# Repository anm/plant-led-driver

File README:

This was designed for grow light but obviously can be rather more general
purpose.

I have made one and it works.

Software incomplete, but may clean up / publish at some point, especially if
there is interest. I didn't do modbus yet but the 485 link works with custom
commands. It could also be persuaded to understand DMX, I believe.

Some idiosyncracities in design becasue of what parts I had. The 5V supply is
just for the MAX485. You could use a MAX3485 or other 3.3V part.

The electrolytic caps and inrush NTC are not needed.

I only tested it up to 700mA (nominal) per channel.

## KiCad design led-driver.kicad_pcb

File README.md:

This was designed for grow light but obviously can be rather more general
purpose. I have made one and it works.

Drivers are PAM2863, controller STM32G030F6P6.

Software incomplete, but may clean up / publish at some point, especially if
there is interest. I didn't do modbus yet but the 485 link works with custom
commands. It could also be persuaded to understand DMX, I believe.

Some idiosyncracities in design becasue of what parts I had. The 5V supply is
just for the MAX485. You could use a MAX3485 or other 3.3V part. The board is
<100x100mm for cheap manufacture, and the components are cheap from LCSC. The
throughhole stuff could be made SMD for cheap manufacture, but I made this for
assembling myself with parts I had.

The electrolytic caps and inrush NTC are not needed.

I designed it for, and tested it up to, 700mA (nominal) per channel. The
drivers can do 2A, and the specified components should also work at 2A, except
that you need to change the current sense resistor to change the maximum
current. Choose resistance according to the table in the datasheet or on the
back of the board, with sufficient power dissapation.

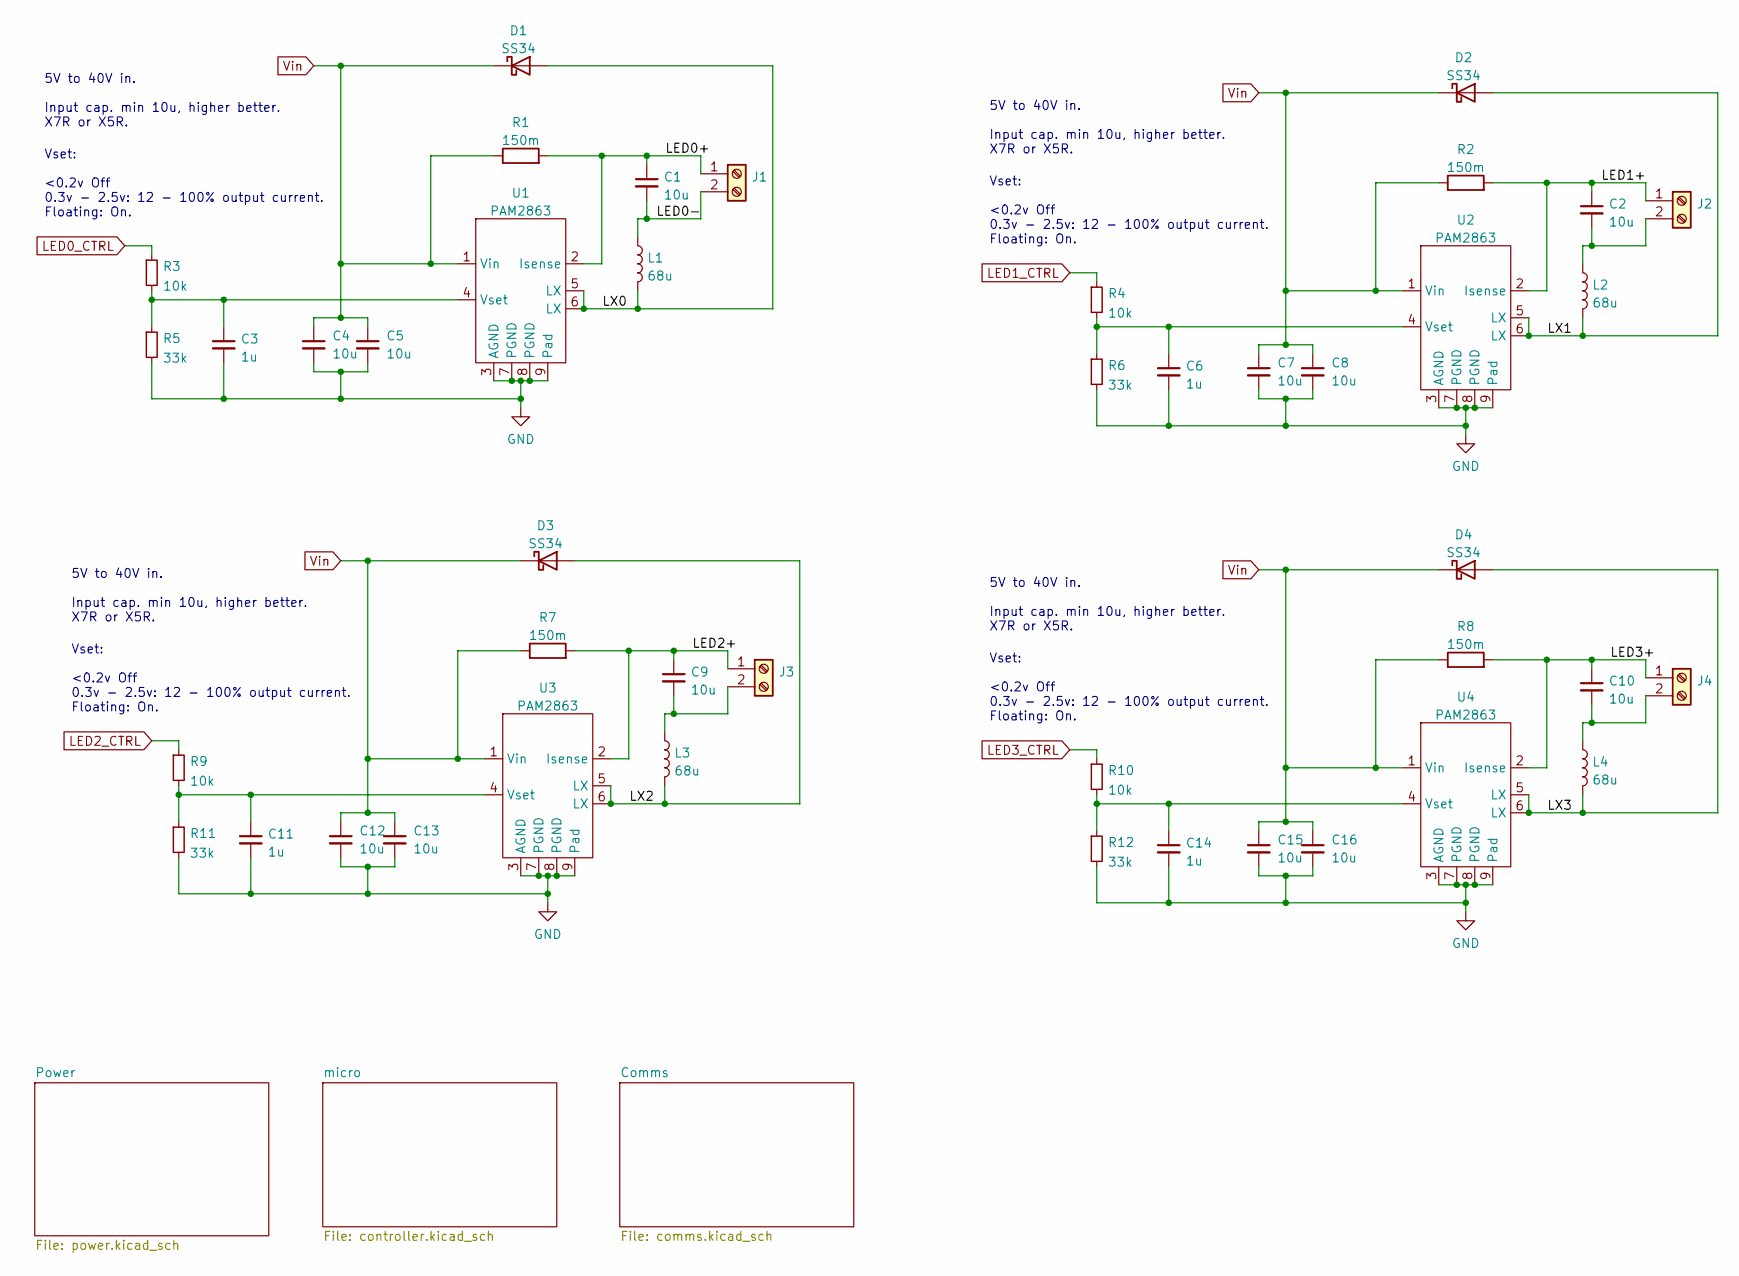
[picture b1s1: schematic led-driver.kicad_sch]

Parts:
C1, C2, C4, C5, C7, C8, C9, C10, C12, C13, C15, C16: 10u; C_1206_3216Metric_Pad1.33x1.80mm_HandSolder; LCSC# C89632
C3, C6, C11, C14: 1u; C_0805_2012Metric
D1, D2, D3, D4: SS34; D_SMA; Part# Slkor SS34; LCSC# C408258
J1, J2, J3, J4: TerminalBlock_KEFENG_Blue_2
L1, L2, L3, L4: 68u; Inductor_SMD_10.2x11.0x5; LCSC# C2837473
R1, R2, R7, R8: 150m; R_2010_5025Metric_Pad1.40x2.65mm_HandSolder; LCSC# C382266
R3, R4, R9, R10: 10k; R_0805_2012Metric
R5, R6, R11, R12: 33k; R_0805_2012Metric
U1, U2, U3, U4: PAM2863; HSOP-8-1EP_3.9x4.9mm_P1.27mm_EP2.41x3.1mm_ThermalVias_0.3mm

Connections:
/LED0+: C1.1, J1.1, R1.2, U1.2 (Isense)
/LED0-: C1.2, J1.2, L1.1
/LED1+: C2.1, J2.1, R2.2, U2.2 (Isense)
/LED2+: C9.1, J3.1, R7.2, U3.2 (Isense)
/LED3+: C10.1, J4.1, R8.2, U4.2 (Isense)
/LX0: D1.2 (A), L1.2, U1.5 (LX), U1.6 (LX)
/LX1: D2.2 (A), L2.2, U2.5 (LX), U2.6 (LX)
/LX2: D3.2 (A), L3.2, U3.5 (LX), U3.6 (LX)
/LX3: D4.2 (A), L4.2, U4.5 (LX), U4.6 (LX)
GND: C3.2, C4.2, C5.2, C6.2, C7.2, C8.2, C11.2, C12.2, C13.2, C14.2, C15.2, C16.2, R5.2, R6.2, R11.2, R12.2, U1.3 (AGND), U1.7 (PGND), U1.8 (PGND), U1.9 (Pad), U2.3 (AGND), U2.7 (PGND), U2.8 (PGND), U2.9 (Pad), U3.3 (AGND), U3.7 (PGND), U3.8 (PGND), U3.9 (Pad), U4.3 (AGND), U4.7 (PGND), U4.8 (PGND), U4.9 (Pad); also elsewhere on the board
LED0_CTRL: R3.1; also elsewhere on the board
LED1_CTRL: R4.1; also elsewhere on the board
LED2_CTRL: R9.1; also elsewhere on the board
LED3_CTRL: R10.1; also elsewhere on the board
unnamed: C2.2, J2.2, L2.1
unnamed: C3.1, R3.2, R5.1, U1.4 (Vset)
unnamed: C6.1, R4.2, R6.1, U2.4 (Vset)
unnamed: C9.2, J3.2, L3.1
unnamed: C10.2, J4.2, L4.1
unnamed: C11.1, R9.2, R11.1, U3.4 (Vset)
unnamed: C14.1, R10.2, R12.1, U4.4 (Vset)
Vin: C4.1, C5.1, C7.1, C8.1, C12.1, C13.1, C15.1, C16.1, D1.1 (K), D2.1 (K), D3.1 (K), D4.1 (K), R1.1, R2.1, R7.1, R8.1, U1.1 (Vin), U2.1 (Vin), U3.1 (Vin), U4.1 (Vin); also elsewhere on the board

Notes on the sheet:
Vset: <0.2v Off 0.3v - 2.5v: 12 - 100% output current. Floating: On.
5V to 40V in. Input cap. min 10u, higher better. X7R or X5R.

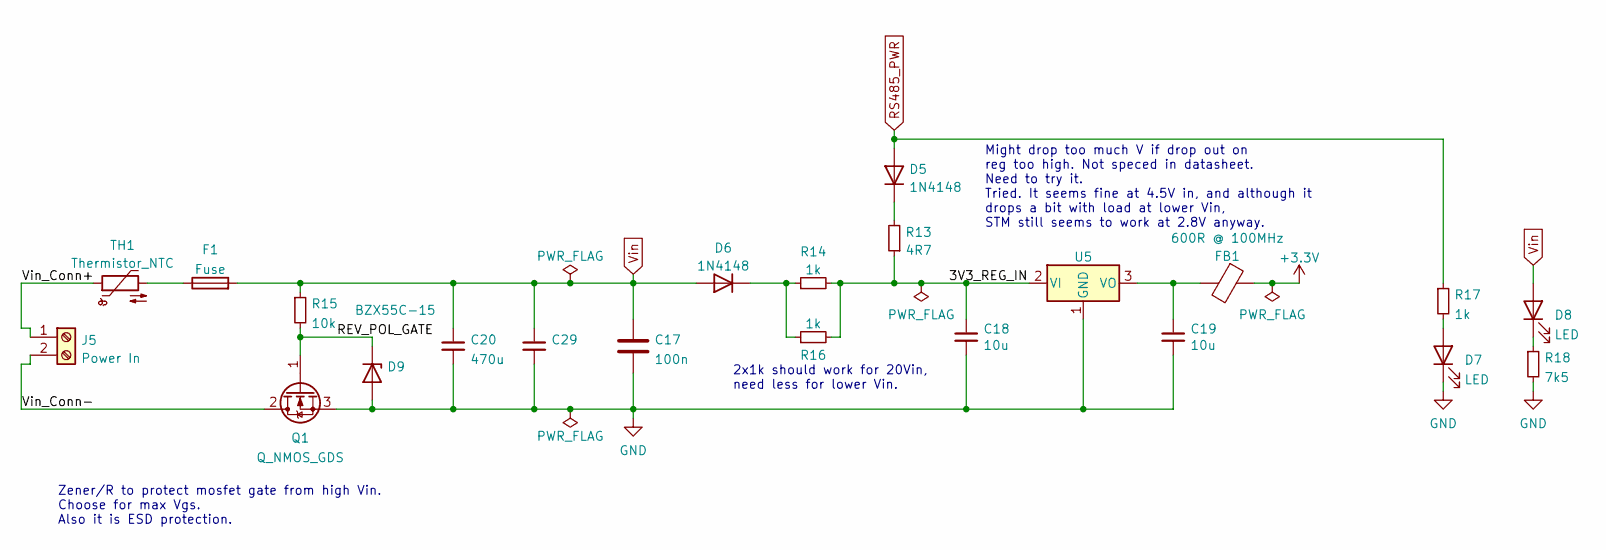
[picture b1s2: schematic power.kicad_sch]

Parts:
C17: 100n; C_0805_2012Metric
C18, C19: 10u; C_0805_2012Metric; Part# CL21A106KAYNNNE; LCSC# C15850
C20: 470u; CP_Radial_D10.0mm_P5.00mm
C29: CP_Radial_D10.0mm_P5.00mm
D5, D6: 1N4148; D_DO-35_SOD27_P7.62mm_Horizontal
D7, D8: LED; LED_0805_2012Metric
D9: BZX55C-15; D_DO-35_SOD27_P7.62mm_Horizontal
F1: Fuse; Fuseholder_Cylinder-5x20mm_Schurter_0031_8201_Horizontal_Op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
FB1: 600R @ 100MHz; L_0805_2012Metric; Part# GZ2012D601TF; LCSC# C1017
J5: Power In; TerminalBlock_KEFENG_Blue_2
Q1: Q_NMOS_GDS; TO-252-3_TabPin2; Part Overspecced but I have some NVD5865NL
R13: 4R7; R_Axial_DIN0309_L9.0mm_D3.2mm_P12.70mm_Horizontal
R14, R16: 1k; R_Axial_DIN0309_L9.0mm_D3.2mm_P12.70mm_Horizontal
R15: 10k; R_0805_2012Metric_Pad1.20x1.40mm_HandSolder
R17: 1k; R_0805_2012Metric
R18: 7k5; R_0805_2012Metric
TH1: Thermistor_NTC; C_Disc_D7.5mm_W5.0mm_P7.50mm
U5: UMW_HT7533-1_3.3V_High-In_LDO_SOT89; SOT-89-3

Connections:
+3V3: FB1.1; also elsewhere on the board
/Power/3V3_REG_IN: C18.1, R13.1, R14.2, R16.2, U5.2 (VI)
/Power/REV_POL_GATE: D9.1 (K), Q1.1 (G), R15.2
/Power/Vin_Conn+: J5.1, TH1.1
/Power/Vin_Conn-: J5.2, Q1.2 (D)
GND: C17.2, C18.2, C19.2, C20.2, C29.2, D7.1 (K), D9.2 (A), Q1.3 (S), R18.2, U5.1 (GND); also elsewhere on the board
unnamed: C19.1, FB1.2, U5.3 (VO)
unnamed: D5.1 (K), R13.2
unnamed: D6.1 (K), R14.1, R16.1
unnamed: D7.2 (A), R17.2
unnamed: D8.1 (K), R18.1
unnamed: F1.1, TH1.2
RS485_PWR: D5.2 (A), R17.1; also elsewhere on the board
Vin: C17.1, C20.1, C29.1, D6.2 (A), D8.2 (A), F1.2, R15.1; also elsewhere on the board

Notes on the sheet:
Might drop too much V if drop out on reg too high. Not speced in datasheet. Need to try it. Tried. It seems fine at 4.5V in, and although it drops a bit with load at lower Vin, STM still seems to work at 2.8V anyway.
2x1k should work for 20Vin, need less for lower Vin.
Zener/R to protect mosfet gate from high Vin. Choose for max Vgs. Also it is ESD protection.

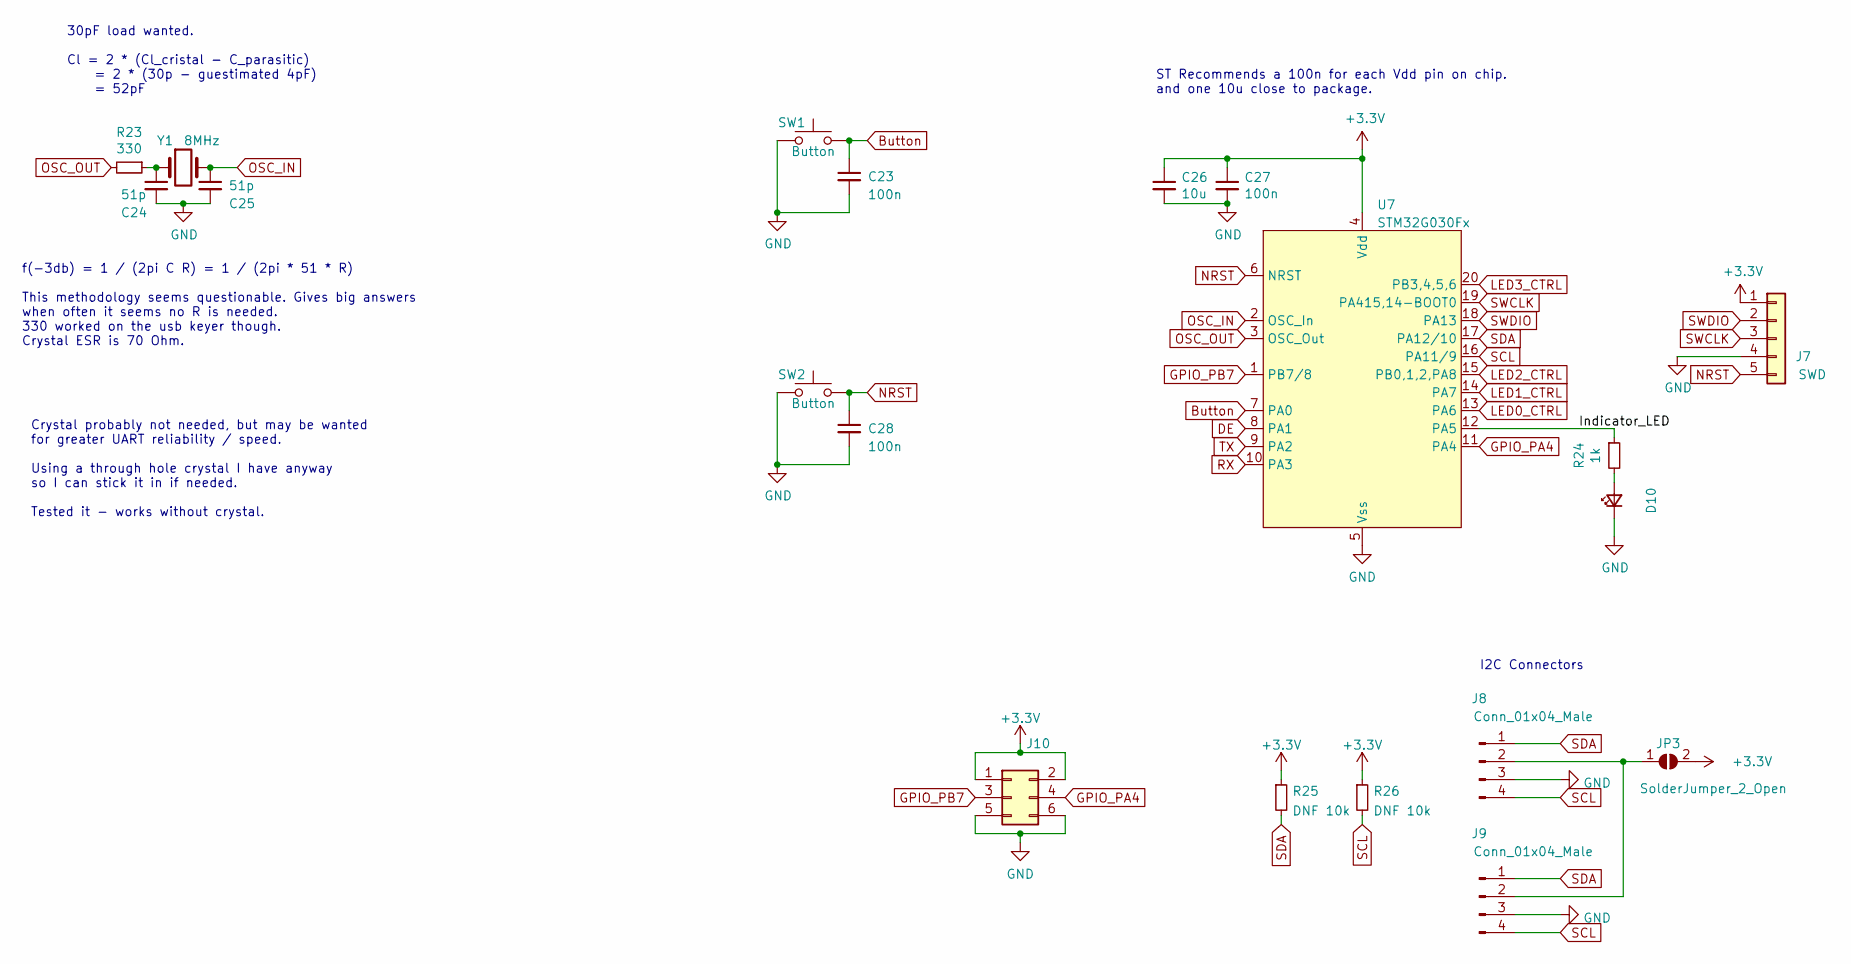
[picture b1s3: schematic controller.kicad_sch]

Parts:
C23, C27, C28: 100n; C_0805_2012Metric; Part# CL05B104KO5NNNC; LCSC# C1525
C24, C25: 51p; C_0603_1608Metric_Pad1.08x0.95mm_HandSolder
C26: 10u; C_0805_2012Metric; Part# CL21A106KAYNNNE; LCSC# C15850
D10: LED_0805_2012Metric; LCSC# C2297
J7: SWD; PinHeader_1x05_P2.54mm_Vertical
J8, J9: Conn_01x04_Male; JST_PH_B4B-PH-K_1x04_P2.00mm_Vertical
J10: Conn_02x03_Counter_Clockwise; PinHeader_2x03_P2.54mm_Vertical
JP3: SolderJumper_2_Open; SolderJumper-2_P1.3mm_Open_TrianglePad1.0x1.5mm
R23: 330; R_0805_2012Metric; LCSC# C17630
R24: 1k; R_0805_2012Metric; LCSC# C17590
R25, R26: DNF 10k; R_0805_2012Metric_Pad1.20x1.40mm_HandSolder
SW1, SW2: Button; SW_SPST_TL3342; LCSC# C412369
U7: STM32G030Fx; TSSOP-20_4.4x6.5mm_P0.65mm
Y1: 8MHz; Crystal_HC49-4H_Vertical

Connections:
+3V3: C26.1, C27.1, J7.1, J10.1, J10.2, JP3.2 (B), R25.1, R26.1, U7.4 (Vdd); also elsewhere on the board
/micro/Indicator_LED: R24.1, U7.12 (PA5)
Button: C23.1, SW1.2, U7.7 (PA0)
DE: U7.8 (PA1); also elsewhere on the board
GND: C23.2, C24.2, C25.2, C26.2, C27.2, C28.2, D10.1 (K), J7.4, J8.3, J9.3, J10.5, J10.6, SW1.1, SW2.1, U7.5 (Vss); also elsewhere on the board
GPIO_PA4: J10.4, U7.11 (PA4)
GPIO_PB7: J10.3, U7.1 (PB7/8)
LED0_CTRL: U7.13 (PA6); also elsewhere on the board
LED1_CTRL: U7.14 (PA7); also elsewhere on the board
LED2_CTRL: U7.15 (PB0,1,2,PA8); also elsewhere on the board
LED3_CTRL: U7.20 (PB3,4,5,6); also elsewhere on the board
NRST: C28.1, J7.5, SW2.2, U7.6 (NRST)
unnamed: C24.1, R23.1, Y1.1
unnamed: D10.2 (A), R24.2
unnamed: J8.2, J9.2, JP3.1 (A)
OSC_IN: C25.1, U7.2 (OSC_In), Y1.2
OSC_OUT: R23.2, U7.3 (OSC_Out)
RX: U7.10 (PA3); also elsewhere on the board
SCL: J8.4, J9.4, R26.2, U7.16 (PA11/9)
SDA: J8.1, J9.1, R25.2, U7.17 (PA12/10)
SWCLK: J7.3, U7.19 (PA415,14-BOOT0)
SWDIO: J7.2, U7.18 (PA13)
TX: U7.9 (PA2); also elsewhere on the board

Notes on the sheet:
ST Recommends a 100n for each Vdd pin on chip. and one 10u close to package.
30pF load wanted. Cl = 2 * (Cl_cristal - C_parasitic) = 2 * (30p - guestimated 4pF) = 52pF
I2C Connectors
Crystal probably not needed, but may be wanted for greater UART reliability / speed. Using a through hole crystal I have anyway so I can stick it in if needed. Tested it - works without crystal.
f(-3db) = 1 / (2pi C R) = 1 / (2pi * 51 * R) This methodology seems questionable. Gives big answers when often it seems no R is needed. 330 worked on the usb keyer though. Crystal ESR is 70 Ohm.

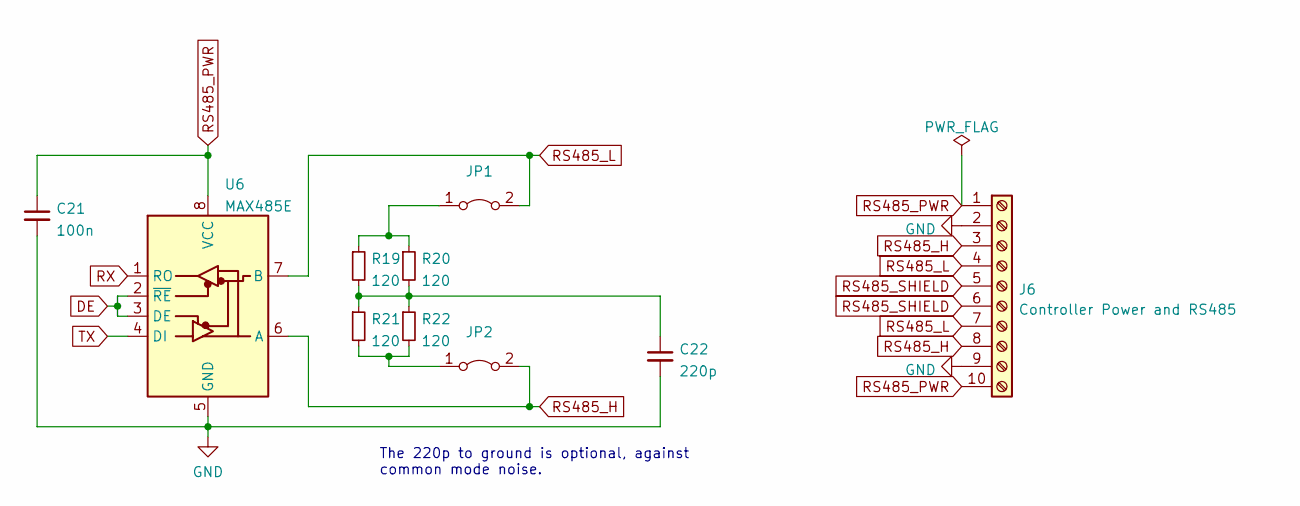
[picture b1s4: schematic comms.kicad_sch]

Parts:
C21: 100n; C_0805_2012Metric
C22: 220p; C_0805_2012Metric
J6: Controller Power and RS485; TerminalBlock_KEFENG_Blue_10
JP1, JP2: PinHeader_1x02_P2.54mm_Vertical
R19, R20, R21, R22: 120; R_0805_2012Metric
U6: MAX485E; DIP-8_W7.62mm_Socket

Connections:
DE: U6.2 (~RE), U6.3 (DE); also elsewhere on the board
GND: C21.2, C22.2, J6.2, J6.9, U6.5 (GND); also elsewhere on the board
unnamed: C22.1, R19.2, R20.2, R21.1, R22.1
unnamed: JP1.1 (A), R19.1, R20.1
unnamed: JP2.1 (A), R21.2, R22.2
RS485_H: J6.3, J6.8, JP2.2 (B), U6.6 (A)
RS485_L: J6.4, J6.7, JP1.2 (B), U6.7 (B)
RS485_PWR: C21.1, J6.1, J6.10, U6.8 (VCC); also elsewhere on the board
RS485_SHIELD: J6.5, J6.6
RX: U6.1 (RO); also elsewhere on the board
TX: U6.4 (DI); also elsewhere on the board

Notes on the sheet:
The 220p to ground is optional, against common mode noise.

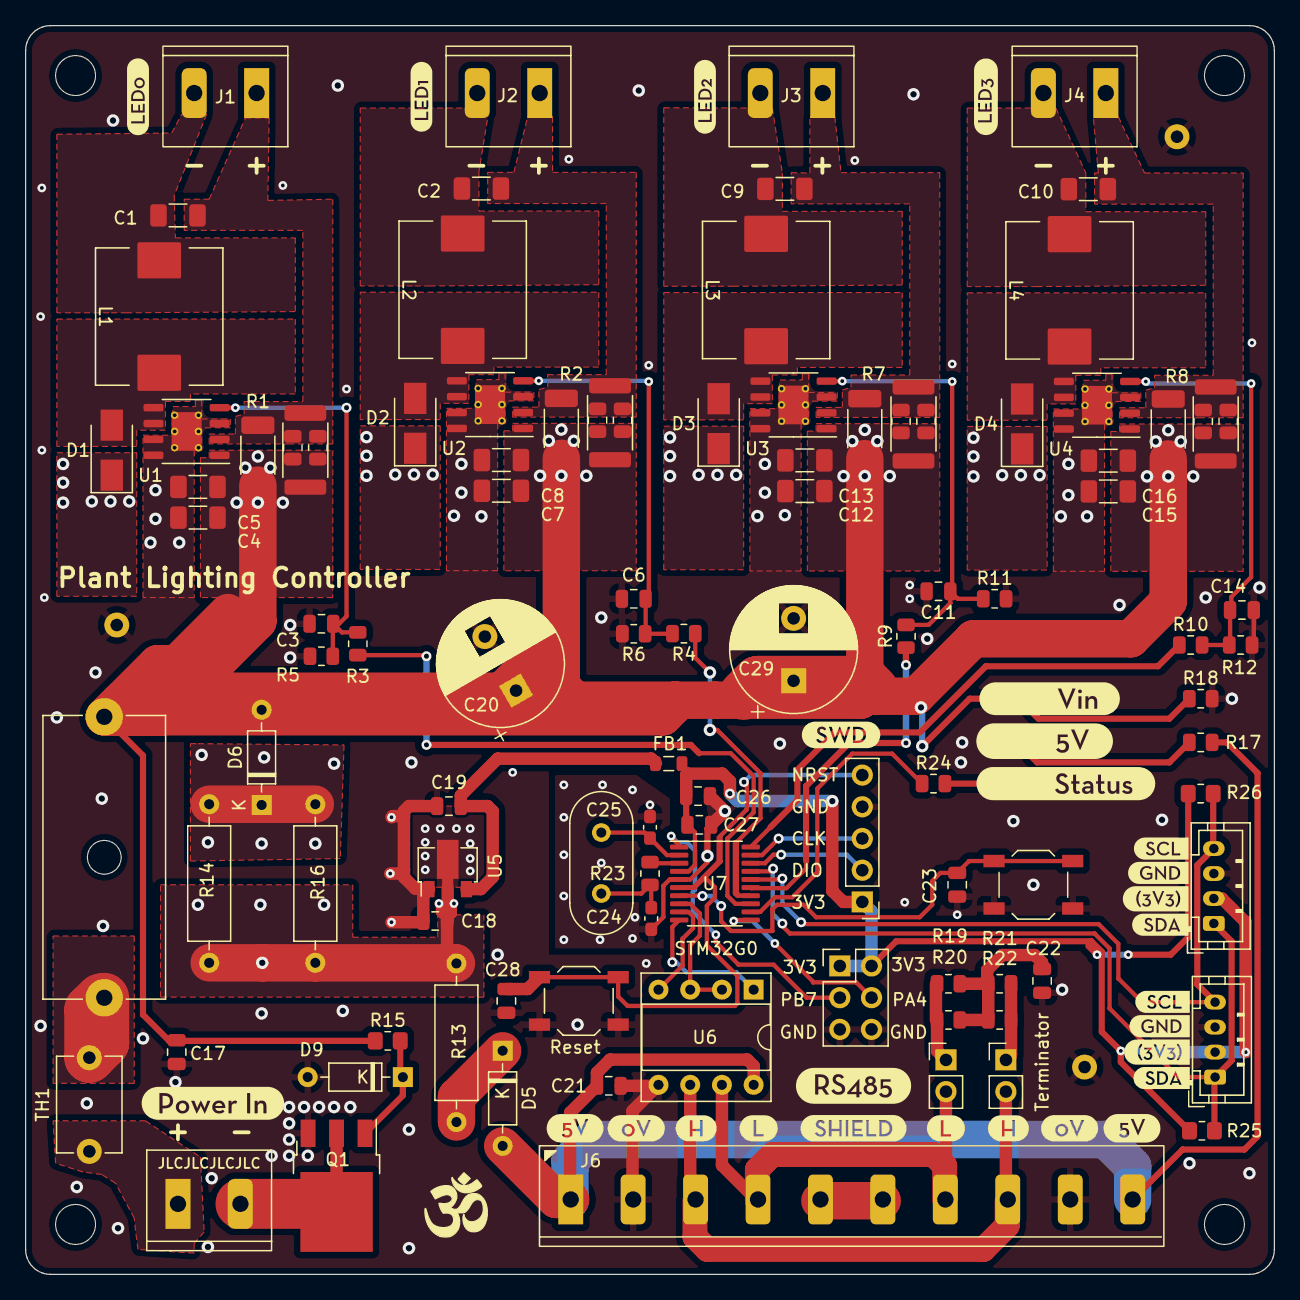
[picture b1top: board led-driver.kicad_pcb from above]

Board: 2 copper layers, 100.0 x 100.0 mm, 123 parts (1 on the bottom side), 57 nets.

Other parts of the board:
kibuzzard-633CB0FB: G***; kibuzzard-633CB0FB
kibuzzard-6276EDEB: G***; kibuzzard-6276EDEB
kibuzzard-6276EF20: G***; kibuzzard-6276EF20
kibuzzard-6276EF29: G***; kibuzzard-6276EF29
kibuzzard-6276EF30: G***; kibuzzard-6276EF30
kibuzzard-62758A42: G***; kibuzzard-62758A42
kibuzzard-62769A2B, kibuzzard-62769A2B#2: G***; kibuzzard-62769A2B
kibuzzard-62770F6E: G***; kibuzzard-62770F6E
kibuzzard-627614DF: G***; kibuzzard-627614DF
kibuzzard-627692FB, kibuzzard-627692FB#2: G***; kibuzzard-627692FB
kibuzzard-6275894F, kibuzzard-6275894F#2: G***; kibuzzard-6275894F
kibuzzard-6275896E, kibuzzard-6275896E#2: G***; kibuzzard-6275896E
kibuzzard-62758962, kibuzzard-62758962#2: G***; kibuzzard-62758962
kibuzzard-62758977, kibuzzard-62758977#2: G***; kibuzzard-62758977
kibuzzard-62758985: G***; kibuzzard-62758985
kibuzzard-62761502: G***; kibuzzard-62761502
kibuzzard-62761516: G***; kibuzzard-62761516
kibuzzard-62769306, kibuzzard-62769306#2: G***; kibuzzard-62769306
kibuzzard-62769315, kibuzzard-62769315#2: G***; kibuzzard-62769315

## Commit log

2022-10-04 v0.2 WIP: Original as manufatured (v0.1) with larger ground vias connected and added labels.
2022-10-04 Added README
2022-10-04 Added board front render.
2022-10-04 Add readme image.
2022-10-04 README chips comment.
2022-10-05 Schematic cleanup and readme improvement.
